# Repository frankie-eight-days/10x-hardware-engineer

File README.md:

# 10x Hardware Engineer

An experiment in agent-driven, full-stack open-source hardware: design a Linux-class dev board from datasheet to shell prompt with as much LLM automation as physically possible, then write up what worked and what didn't.

## The board

**Target MPU:** NXP i.MX 6ULL (MCIMX6Y2CVM08AB, ~$5–6 @ qty 10)
- Cortex-A7 @ 800 MHz, MAPBGA-289, 0.8 mm pitch (forgiving for an open-stack BGA fanout)
- External DDR3, 2× 10/100 Ethernet MAC, USB 2.0 OTG, I²S, UART, SPI, USDHC
- Mainline Linux + U-Boot, NXP Yocto BSP, Olimex OLinuXino open KiCad reference

**Peripherals (v1 spec):**
- 256–512 MB DDR3L (Micron / Nanya, 16-bit, JLC stock permitting)
- 1× RJ45 Ethernet (LAN8720A or KSZ8081 PHY) — talk to it over the home LAN
- USB 2.0 host/OTG (also doubles as i.MX serial-download recovery — unbrick without JTAG)
- microSD slot (primary boot)
- Optional QSPI / eMMC footprint (stretch)
- I²S Class-D audio amp (MAX98357A) + speaker pads — fun ngspice subject
- USB-UART bridge (CH340N, JLC Basic) for the shell, plus 4-pin TTL UART header
- 10-pin Cortex JTAG/SWD header (don't ship without it)
- PMIC: PCA9450 or PF3000 (TBD — pick what JLC has stocked)

## The stack

| Layer | Tool | Notes |
|---|---|---|
| Datasheet RAG | Docling → LanceDB hybrid → custom FastMCP | Required citations on every answer |
| Block diagrams | Mermaid (source-of-truth) + drawio MCP | mermaid diffs in git, drawio for blog |
| Schematic | atopile (`.ato`) | parametric `pick_part`, JLC-aware |
| Parts | jlcparts SQLite + easyeda2kicad | offline part DB + symbol/footprint pulls |
| Layout | KiCad 9 + Seeed kicad-mcp-server | 39-tool MCP |
| Routing | KiCad PNS (DDR3, USB, ENET) + Freerouting CLI (boring nets) | hybrid; agent does length-tune constraints |
| Sim | ngspice + InSpice | power rails, PMIC loop, Class-D filter |
| Fab/PCBA | JLCPCB API | basic/preferred parts where possible |
| Firmware build | Buildroot + mainline U-Boot + mainline Linux | Yocto is overkill |
| Firmware debug | OpenOCD + JTAG + serial-download recovery | |
| LLM | Opus 4.7 (1M) for layout/DDR; Sonnet 4.6 for cheap Q&A | prompt-cache datasheet + HDG |

## Phases

1. **Hardware capture** — block diagram → atopile modules → KiCad netlist → BOM
2. **Layout** — placement, BGA escape, DDR3 length-matching, Ethernet diff pairs, fab files
3. **Bring-up** — power-on, UART, U-Boot from SD
4. **Linux** — kernel + Buildroot rootfs, shell over UART
5. **Network** — DHCP, SSH from laptop
6. **Audio demo** — I²S out to the Class-D amp, play a sine wave from userland
7. **Blog** — honest write-up: what the agents did, what they got wrong, where humans had to step in

## Why this is supposed to be novel

Quilter shipped an i.MX 8M Mini DDR4 board with an autonomous physics engine in 40 hours — closed-source. atopile / tscircuit / Diode have shipped public LLM-driven schematics but only on 2-layer ESP32-class boards. **Nobody has publicly crossed the DDR Rubicon on a fully open agent stack.** That's the gap.

## Status

Scaffolding. See [PLAN.md](PLAN.md) for the decision log and open questions.

## License

MIT.

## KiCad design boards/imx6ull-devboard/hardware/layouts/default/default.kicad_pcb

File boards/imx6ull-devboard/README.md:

# i.MX 6ULL Dev Board

See repo root [README.md](../../README.md) and [PLAN.md](../../PLAN.md).

## Layout

- `hardware/` — atopile sources, KiCad project, mermaid block diagrams, ngspice decks
- `firmware/` — Buildroot config, U-Boot patches, Linux device tree

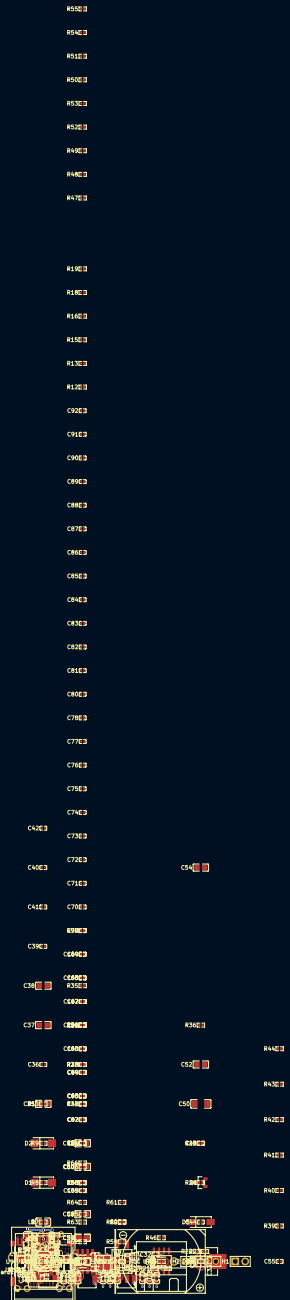
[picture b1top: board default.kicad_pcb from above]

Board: 2 copper layers, 218 parts (0 on the bottom side), 172 nets.

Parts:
B1: BAT-TH_CR2032-BS-6-1
C1, C2, C3, C4, C10, C13, C17, C20, C24, C27, C36, C39, C43, C44, C45, C46, C49, C51, C53, C55, C65, C69, C70, C71, C72, C73, C74, C75, C76, C77, C78, C79, C80, C81, C82, C83, C84, C85, C86, C87, C88, C89, C90, C91, C92, C95, C96, C97, C98, C99, C100, C101, C102, C103, C104, C105, C106, C107, C108: 100nF ±10%; C0402
C5, C6, C31, C32, C33, C34, C48, C59, C61, C62, C63, C64: 1µF ±10%; C0402
C7: 470pF ±10%; C0402
C8, C9: 18pF ±5%; C0402
C11, C12, C18, C19, C25, C26, C37, C38, C47, C52, C56, C57, C60, C93, C94: 10µF ±10%; C0805
C14, C15, C16, C21, C22, C23, C28, C29, C30: 100nF ±10%; C0603
C35, C54, C58: 22µF ±20%; C0805
C40, C41, C42: 470nF ±10%; C0402
C50: 100µF ±20%; C1206
C66: 10nF ±10%; C0402
C67, C68: 22pF ±5%; C0402
C109: 1nF ±10%; C0805
CN1: CONN-TH_2P-P6.35_DB910-6.35-2P
CN2: CONN-SMD_1310-1205G0M061CR02
Card1: TF-SMD_TF-015
D1, D2: Vf {ℝ+}V; SMA_L4.3-W2.6-LS5.2-RD
D3, D6, D9: SOT-23-6_L2.9-W1.6-P0.95-LS2.8-BL
D4, D5: Vf {ℝ+}V; SMA_L4.4-W2.8-LS5.4-R-RD
F1, F2, F3: F0805
H1: HDR-TH_2P-P2.54-V-M
H2: HDR-TH_4P-P2.54-V-M
J1: RJ45-TH_HR911105A
L1, L2, L3: L 2.2µH ±20%; IND-SMD_L4.4-W4.2
L4, L5: L {ℝ+}H; L0805
Q1: Vgs ℝ+V; SOT-23_L2.9-W1.3-P1.90-LS2.4-BR
R1: 4.75kΩ ±1%; R0402
R2: 1.5kΩ ±1%; R0402
R3, R5, R28, R30, R45: 100kΩ ±1%; R0402
R4: 12.1kΩ ±1%; R0402
R6, R11, R13, R14, R15, R16, R17, R19, R31, R36, R39, R40, R44, R50, R52, R54, R59: 10kΩ ±1%; R0402
R7, R8, R9, R10: 49.9Ω ±1%; R0402
R12, R60, R61: 4.7kΩ ±1%; R0402
R18, R41, R47, R48: 1kΩ ±1%; R0402
R20: 6.34kΩ ±0.1%; R0402
R21: 2.8kΩ ±1%; R0402
R22: 13.7kΩ ±1%; R0402
R23: 16.9kΩ ±1%; R0402
R24, R25: 33Ω ±1%; R0402
R26, R27, R37, R38, R57, R58: 10kΩ ±1%; R0603
R29, R62: 1MΩ ±1%; R0402
R32, R33, R34, R35: 47kΩ ±1%; R0402
R42, R43: 680Ω ±1%; R0402
R46: 100Ω ±1%; R0402
R49, R56: 240Ω ±1%; R0402
R51: 8.2kΩ ±1%; R0402
R53: 7.5kΩ ±1%; R0402
R55: 33kΩ ±1%; R0402
R63, R64: 330Ω ±1%; R0402
R65, R66: 75Ω ±1%; R0402
SW1: SW-SMD_DSIC02LSGET
SW2: SW-SMD_4P-L5.1-W5.1-P3.70-LS6.5-TL_H1.5
U1: QFN-24_L4.0-W4.0-P0.50-TL-EP2.5
U2, U3, U4: SOT-23-6_L2.9-W1.6-P0.95-LS2.8-BR
U5: WSON-6_L2.0-W2.0-P0.65-TL-EP
U6: SOT-23-5_L3.0-W1.7-P0.95-LS2.8-BL
U7: SOP-8_L4.9-W3.9-P1.27-LS6.0-BL
U8: TQFN-16_L3.0-W3.0-P0.50-BL-EP1.5
U9: BGA-289_L14.0-W14.0-R17-C17-P0.80-BL
U10: TFBGA-96_L13.0-W7.5-R16-C6-P0.80-TL
U11: SOIC-8_L5.0-W4.0-P1.27-LS6.0-BL
USB1, USB2, USB3: USB-C-SMD_TYPE-C-6PIN-2MD-073
X1: OSC-SMD_4P-L3.2-W2.5-BL_SIT8008BI
X2: CRYSTAL-SMD_4P-L3.2-W2.5-BL
X3, X4: FC-135R_L3.2-W1.5

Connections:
1: U11.1, X4.1
2: U11.2, X4.2
4: R26.1, USB1.4
10: R27.1, USB1.10
A2: U9.P3, U10.A2
A3: U9.R1, U10.A3
A7: U9.P5, U10.A7
B8: U9.R2, U10.B8
BA0: U9.M1, U10.M2
BA1: U9.H1, U10.N8
BA2: U9.K2, U10.M3
BOB_SMITH: C109.1, R65.2, R66.2
C2: U9.R4, U10.C2
C3: U9.U3, U10.C3
C8: U9.U5, U10.C8
CD: Card1.9, R30.1, U9.M15
CDDAT3CS: Card1.2, R35.1, U9.A2
CHASSIS_GND: C109.2, J1.SH1, J1.SH2, R62.1
CK: U9.P1, U10.J7
CKE: U9.M3, U10.K9
CLKSCLK: Card1.5, U9.C1
CMDDI: Card1.3, R31.1, U9.C2
D7: U9.U2, U10.D7
DAT1RSV: Card1.8, R33.1, U9.B2
DAT2RSV: Card1.1, R34.1, U9.B1
DATA_N: D3.1, D3.6, U7.2, USB1.5, USB1.7
DATA_P: D3.3, D3.4, U7.1, USB1.6, USB1.8
DDR_A0: U9.L5, U10.N3
DDR_A4: U9.K4, U10.P8
DDR_A5: U9.L1, U10.P2
DDR_A6: U9.G2, U10.R8
DDR_A10_AP: U9.M4, U10.L7
DDR_A11: U9.K3, U10.R7
DDR_A12_nBC: U9.L4, U10.N7
DDR_A13: U9.H3, U10.T3
DML: U9.T7, U10.E7
DMU: U9.T3, U10.D3
DQL0: U9.T4, U10.E3
DQL1: U9.U6, U10.F7
DQL2: U9.T6, U10.F2
DQL3: U9.U7, U10.F8
DQL4: U9.U8, U10.H3
DQL5: U9.T8, U10.H8
DQL6: U9.T5, U10.G2
DQL7: U9.U4, U10.H7
DQSL: U9.P6, U10.G3
DQSU: U9.T1, U10.C7
DRAM_ADDR01: U9.H2, U10.P7
DRAM_ADDR02: U9.K1, U10.P3
DRAM_ADDR03: U9.M2, U10.N2
DRAM_ADDR07: U9.H4, U10.R2
DRAM_ADDR08: U9.J4, U10.T8
DRAM_ADDR09: U9.L2, U10.R3
DRAM_CAS_B: U9.J2, U10.K3
DRAM_CS0_B: U9.N2, U10.L2
DRAM_RAS_B: U9.M5, U10.J3
DRAM_RESET: U9.G4, U10.T2
DRAM_SDCLK0_N: U9.P2, U10.K7
DRAM_SDQS0_N: U9.P7, U10.F3
DRAM_SDQS1_N: U9.T2, U10.B7
DRAM_SDWE_B: U9.J1, U10.L3
DRAM_ZQPAD: R49.1, U9.N4
ENET1_RX_EN: U1.11, U9.E16
ENET1_RX_ER: R3.1, U1.10, U9.D15
ENET1_TX_CLK: U1.14, U9.F14
ENET1_TX_EN: U1.16, U9.F15
ETH_LED_LINK: J1.10, R5.1, U1.3
ETH_LED_SPEED: J1.12, R1.1, U1.2
ETH_N0_N: J1.8, R7.1, U1.22
ETH_N1_N: J1.3, R9.1, U1.20
ETH_P0_P: J1.4, R8.1, U1.23
ETH_P1_P: J1.1, R10.1, U1.21
GAIN_SLOT: R28.1, U8.2
GPIO1_IO00: R45.1, U9.K13
JTAG_MOD: R12.1, U9.P15
LED1_A: J1.9, R63.2
LED2_A: J1.11, R64.2
N_C_: U8.5, U8.6, U8.12, U8.13
N_TRST: R19.1, U9.N14
ODT: U9.N1, U10.K1
ONOFF: R13.1, U9.R8
POS: B1.1, R41.1
RBIAS: R4.1, U1.24
RTC_XTALI: U9.T11, X3.1
RTC_XTALO: U9.U11, X3.2
RX: H2.4, R25.2, U9.J16
RXD: R24.1, U7.7
RX_CT: J1.7, R65.1
SCK: U8.16, U9.D9
SCL: R60.1, U9.G17, U11.6
SD: U8.1, U9.E9
SDA: R61.1, U9.G16, U11.5
SW1A: R40.1, SW1.1, U9.U10
SW2A: R39.1, SW1.2, U9.T10
TCK: CN2.4, U9.M14
TDI: CN2.8, U9.N16
TDO: CN2.6, U9.N15
TEST_MODE: R18.1, U9.N7
TMS: CN2.2, U9.P14
TX: H2.3, R24.2, U9.J17
TXD: R25.1, U7.6
TX_CT: J1.2, R66.1
UART1_CTS_B: U1.13, U9.K15
UART1_RTS_B: R2.1, U1.12, U9.J14
USB_OTG1_VBUS: R46.2, U9.T12
VDD_SOC_IN: U9.H9, U9.H10, U9.J9, U9.J10, U9.K9, U9.K10
VFB: R52.1, R53.2, U3.4
WS: U8.14, U9.B8
ZQ: R56.1, U10.L8
_buck_1v35_out-hv: L2.2, L4.1, R53.1
_ldo_snvs_out-anode: C34.1, D2.2, R22.1, U6.5
_reset-line: R6.1, R15.1, U1.15, U9.L14
bootstrap_cap-power-hv: C17.1, U3.6
bootstrap_cap-power-hv-1: C10.1, U2.6
bootstrap_cap-power-hv-2: C24.1, U4.6
bootstrap_cap-power-lv: C17.2, L2.1, U3.2
bootstrap_cap-power-lv-1: C10.2, L1.1, U2.2
bootstrap_cap-power-lv-2: C24.2, L3.1, U4.2
c_rst_db-power-hv: C55.1, CN2.10, R16.1, R44.1, SW2.1, U9.P8
cap_ud_dram-power-hv: C61.1, U9.N6
cap_ud_high-power-hv: C62.1, U9.R14, U9.R15
cap_ud_snvs-power-hv: C63.1, U9.N12
cap_ud_usb-power-hv: C64.1, U9.R12
cap_vref_lf-power-hv: C65.1, C66.1, R47.1, R48.2, U9.P4, U10.H1, U10.M8
cap_xtal_a-power-hv: C67.1, U9.T16, X2.1
cap_xtal_b-power-hv: C68.1, U9.T17, X2.3
cathode: B1.2, C1.2, C2.2, C3.2, C4.2, C5.2, C6.2, C7.2, C8.2, C9.2, C31.2, C33.2, C34.2, C35.2, C36.2, C37.2, C38.2, C39.2, C40.2, C41.2, C42.2, C43.2, C44.2, C45.2, C46.2, C47.2, C48.2, C49.2, C50.2, C51.2, C52.2, C53.2, C54.2, C55.2, C56.2, C57.2, C58.2, C59.2, C60.2, C61.2, C62.2, C63.2, C64.2, C65.2, C66.2, C67.2, C68.2, C69.2, C70.2, C71.2, C72.2, C73.2, C74.2, C75.2, C76.2, C77.2, C78.2, C79.2, C80.2, C81.2, C82.2, C83.2, C84.2, C85.2, C86.2, C87.2, C88.2, C89.2, C90.2, C91.2, C92.2, C93.2, C94.2, C95.2, C96.2, C97.2, C98.2, C99.2, C100.2, C101.2, C102.2, C103.2, C104.2, C105.2, C106.2, C107.2, C108.2, CN1.2, CN2.3, CN2.5, CN2.9, Card1.6, Card1.10, Card1.11, Card1.12, Card1.13, D3.2, D6.2, D9.2, H2.1, R1.2, R3.2, R4.2, R5.2, R12.2, R15.2, R18.2, R23.2, R26.2, R27.2, R28.2, R36.2, R37.2, R38.2, R47.2, R49.2, R50.2, R52.2, R54.2, R56.2, R57.2, R58.2, R62.2, SW1.3, SW1.4, SW2.3, U1.25, U2.1, U3.1, U4.1, U5.3, U6.2, U7.3, U8.3, U8.11, U8.15, U8.17, U9.A1, U9.A17, U9.C3, U9.C7, U9.C11, U9.C15, U9.E8, U9.E11, U9.F6, U9.F7, U9.F8, U9.F9, U9.F10, U9.F11, U9.F12, U9.G3, U9.G5, U9.G7, U9.G12, U9.G15, U9.H7, U9.H12, U9.J5, U9.J7, U9.J12, U9.K7, U9.K12, U9.L3, U9.L7, U9.L12, U9.M7, U9.M8, U9.M9, U9.M10, U9.M11, U9.N3, U9.N5, U9.R3, U9.R5, U9.R7, U9.R11, U9.R16, U9.R17, U9.T14, U9.U1, U9.U14, U9.U17, U10.A9, U10.B1, U10.B3, U10.B9, U10.D1, U10.D8, U10.E1, U10.E2, U10.E8, U10.F9, U10.G1, U10.G8, U10.G9, U10.J2, U10.J8, U10.M1, U10.M9, U10.P1, U10.P9, U10.T1, U10.T9, U11.4, USB1.1, USB1.12, USB1.13, USB1.14, USB1.15, USB1.16, USB2.1, USB2.12, USB2.13, USB2.14, USB2.15, USB2.16, USB3.1, USB3.12, USB3.13, USB3.14, USB3.15, USB3.16, X1.2, X1.4, X2.2, X2.4
connector-cc[0]-4: R57.1, USB3.4
connector-cc[0]-4-1: R37.1, USB2.4
connector-cc[1]-10: R58.1, USB3.10
connector-cc[1]-10-1: R38.1, USB2.10
connector-power_vbus-hv: F1.1, USB1.2, USB1.11
connector-power_vbus-hv-1: F3.1, USB3.2, USB3.11
connector-power_vbus-hv-2: F2.1, USB2.2, USB2.11
dat[0]-line: Card1.7, R32.1, U9.B3
decoupling_capacitor-power-hv: C45.1, D3.5, F1.2
en_delay_1v4-power-hv: C40.1, R11.1, U2.5
en_delay_1v35-power-hv: C41.1, R14.1, U3.5
en_delay_3v3-power-hv: C42.1, R17.1, U4.5
feedback_divider-ref_out-hv: R20.2, R21.1, U5.2
feedback_divider-ref_out-hv-1: R22.2, R23.1, U6.4
gate: Q1.1, R36.1
hv: C43.1, U7.8
line: R42.1, U9.L17
lv: C32.2, R21.2, U5.7
nINT: R59.1, U9.M16, U11.3
nSD_MODE: R29.1, U8.4
or_bench-anode: D4.1, Q1.2
phy-rmii-line: U1.18, U9.E14
phy-rmii-line-1: U1.17, U9.E15
phy-rmii-line-2: U1.7, U9.E17
phy-rmii-line-3: U1.8, U9.F16
pin_in-POS: CN1.1, Q1.3
power-anode: C53.1, D5.1, D6.5, F2.2
power_1v4_arm-hv: C57.1, C80.1, C81.1, C82.1, C83.1, L1.2, L5.1, R51.1, U9.G9, U9.G10, U9.G11, U9.H11
power_1v4_soc-hv: C38.1, C39.1, C60.1, C91.1, C92.1, L5.2, U9.G8, U9.H8, U9.J8, U9.J11, U9.K8, U9.K11, U9.L8, U9.L9, U9.L10, U9.L11
power_1v8-hv: C32.1, R20.1, U5.1
power_1v35-hv: C35.1, C36.1, C58.1, C84.1, C85.1, C86.1, C87.1, C88.1, C89.1, C93.1, C94.1, C95.1, C96.1, C97.1, C98.1, C99.1, C100.1, C101.1, C102.1, C103.1, C104.1, C105.1, C106.1, L4.2, R48.1, U9.G6, U9.H6, U9.J6, U9.K6, U9.L6, U9.M6, U10.A1, U10.A8, U10.B2, U10.C1, U10.C9, U10.D2, U10.D9, U10.E9, U10.F1, U10.G7, U10.H2, U10.H9, U10.K2, U10.K8, U10.N1, U10.N9, U10.R1, U10.R9
power_3v3-cathode: C1.1, C2.1, C3.1, C4.1, C5.1, C31.1, C37.1, C46.1, C47.1, C48.1, C51.1, C54.1, C56.1, C59.1, C69.1, C70.1, C71.1, C72.1, C73.1, C74.1, C75.1, C76.1, C77.1, C78.1, C79.1, C90.1, C107.1, C108.1, CN2.1, Card1.4, D1.1, D2.1, D9.5, F3.2, H2.2, L3.2, R2.2, R6.2, R7.2, R8.2, R9.2, R10.2, R13.2, R16.2, R19.2, R29.2, R30.2, R31.2, R32.2, R33.2, R34.2, R35.2, R39.2, R40.2, R43.1, R44.2, R45.2, R46.1, R55.1, R59.2, R60.2, R61.2, R63.1, R64.1, U1.1, U1.9, U1.19, U5.4, U5.6, U8.7, U8.8, U9.C4, U9.E7, U9.E13, U9.F4, U9.F13, U9.H13, U9.J13, U9.L13, U9.M13, U9.N13, U9.P12, U9.P13, U11.8
power_5v-cathode: C33.1, C44.1, C49.1, C50.1, C52.1, D4.2, D5.2, R11.2, R14.2, R17.2, U2.3, U3.3, U4.3, U6.1, U6.3, U7.5
psu.buck_1v4-VFB: R50.1, R51.2, U2.4
psu.buck_3v3-VFB: R54.1, R55.2, U4.4
speaker_n: H1.2, U8.10
speaker_p: H1.1, U8.9
usb_dp_dn-DATA_N: D9.1, D9.6, U9.T15, USB3.5, USB3.7
usb_dp_dn-DATA_P: D9.3, D9.4, U9.U15, USB3.6, USB3.8
usbc_pd-usb-DATA_N: D6.1, D6.6, USB2.5, USB2.7
usbc_pd-usb-DATA_P: D6.3, D6.4, USB2.6, USB2.8
vbat_in-anode: D1.2, R41.2
vddcr_caps[1]-power-hv: C6.1, C7.1, U1.6
xtal_caps[0]-power-hv: C8.1, U1.5, X1.1
xtal_caps[1]-power-hv: C9.1, U1.4, X1.3
